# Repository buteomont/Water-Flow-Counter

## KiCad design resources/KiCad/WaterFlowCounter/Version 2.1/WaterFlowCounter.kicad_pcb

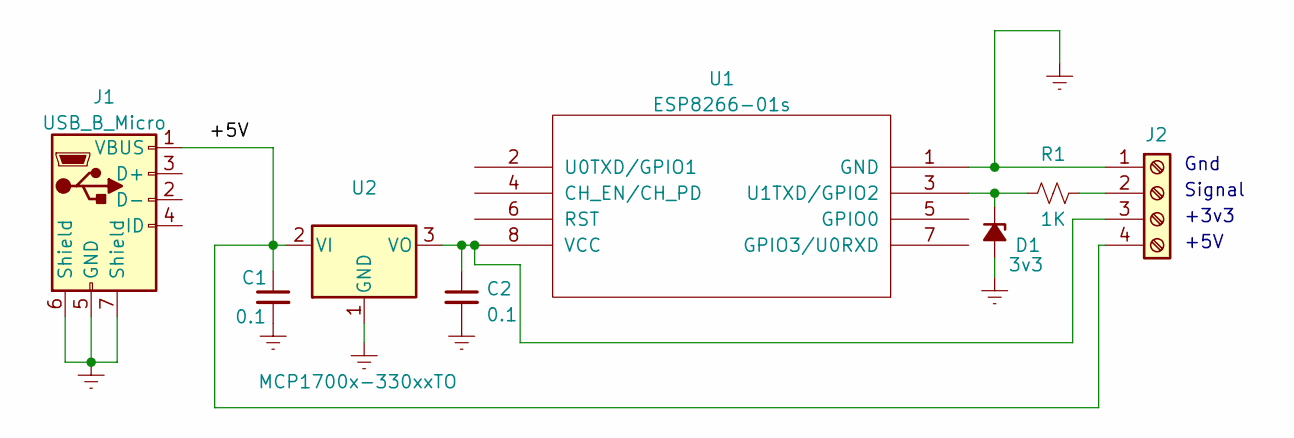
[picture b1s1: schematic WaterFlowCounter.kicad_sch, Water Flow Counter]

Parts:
C1, C2: 0.1; C_Disc_D3.0mm_W1.6mm_P2.50mm
D1: 3v3; D_A-405_P7.62mm_Horizontal
J1: USB_B_Micro; HW-769 Mini USB Socket Board
J2: Screw_Terminal_01x04; Screw Terminal Block x2 P3mm W685 H660
R1: 1K; R_Axial_DIN0204_L3.6mm_D1.6mm_P7.62mm_Horizontal
U1: ESP8266-01s
U2: MCP1700x-330xxTO; TO-92_Inline

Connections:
Earth: C1.2, C2.2, D1.2 (A), J1.5 (GND), J1.6 (Shield), J1.7 (Shield), J2.1, U1.1 (GND), U2.1 (GND)
unnamed: C1.1, J1.1 (VBUS), J2.4, U2.2 (VI)
unnamed: C2.1, J2.3, U1.8 (VCC), U2.3 (VO)
unnamed: D1.1 (K), R1.1, U1.3 (U1TXD/GPIO2)
unnamed: J2.2, R1.2

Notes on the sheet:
+3v3
+5V
Signal
Gnd

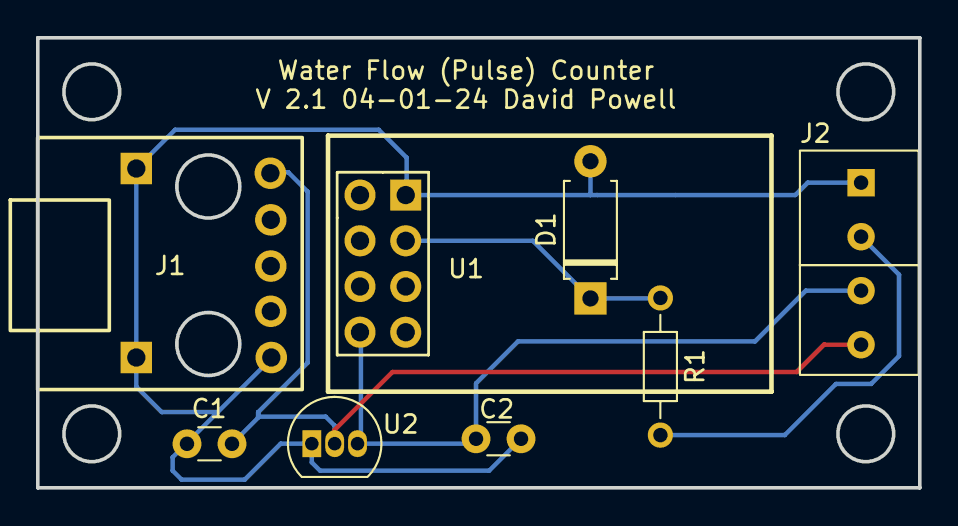
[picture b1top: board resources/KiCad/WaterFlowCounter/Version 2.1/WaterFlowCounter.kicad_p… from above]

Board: 2 copper layers, 49.0 x 25.0 mm, 8 parts (0 on the bottom side), 5 nets.

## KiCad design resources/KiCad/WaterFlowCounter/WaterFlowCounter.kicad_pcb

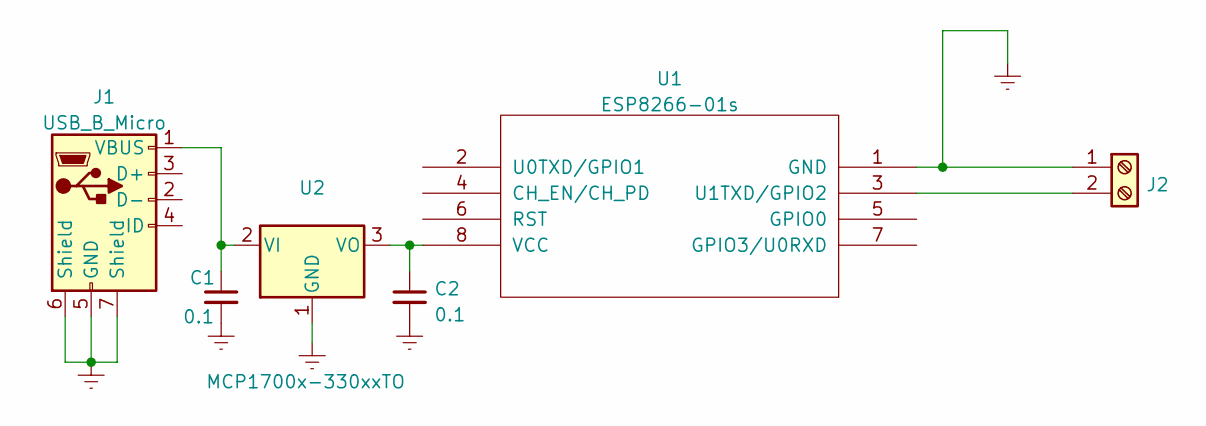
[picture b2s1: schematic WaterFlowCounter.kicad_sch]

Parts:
C1, C2: 0.1; C_Disc_D3.0mm_W1.6mm_P2.50mm
J1: USB_B_Micro; HW-769 Mini USB Socket Board
J2: Screw_Terminal_01x02; Screw Terminal Block P3mm W685 H660
U1: ESP8266-01s
U2: MCP1700x-330xxTO; TO-92_Inline

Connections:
Earth: C1.2, C2.2, J1.5 (GND), J1.6 (Shield), J1.7 (Shield), J2.1, U1.1 (GND), U2.1 (GND)
unnamed: J2.2, U1.3 (U1TXD/GPIO2)
unnamed: C2.1, U1.8 (VCC), U2.3 (VO)
unnamed: C1.1, J1.1 (VBUS), U2.2 (VI)

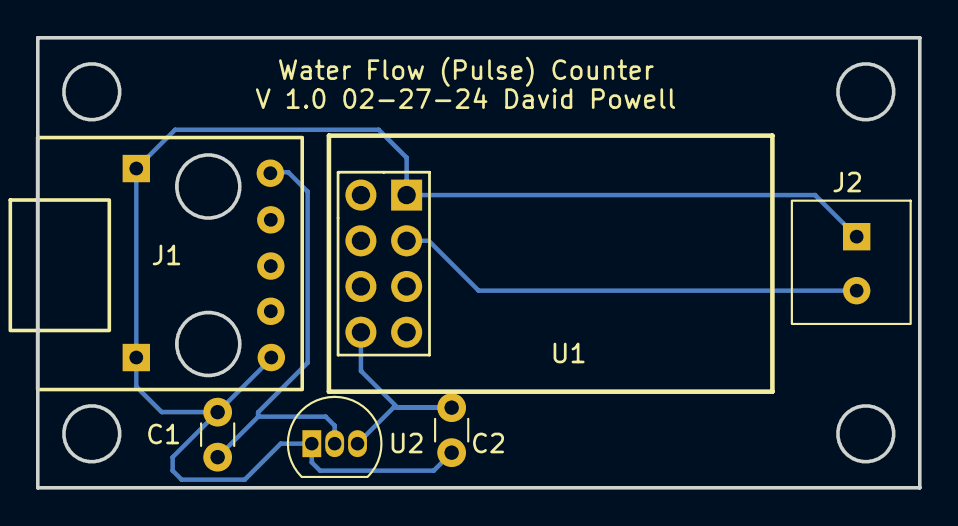
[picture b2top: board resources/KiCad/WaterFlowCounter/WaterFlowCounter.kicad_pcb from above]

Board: 2 copper layers, 49.0 x 25.0 mm, 6 parts (0 on the bottom side), 4 nets.

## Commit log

2024-02-24 Migrate to PlatformIO and improve
2024-02-25 Moved to an interrupt-based model
2024-03-07 lots of changes
2024-03-19 Modified board to present voltages externally
2024-03-20 Added support for the D1 mini (Wemos)
2024-03-20 Updated default pulses per liter value
2024-03-20 Fixed invalid JSON for settings MQTT
2024-03-22 Several adjustments
2024-03-22 Added function to set pulse count
2024-04-02 Minor code changes, added resistor to schematic and board
2024-04-16 Modified interrupt handling
2024-04-19 Added sensorType to settings
